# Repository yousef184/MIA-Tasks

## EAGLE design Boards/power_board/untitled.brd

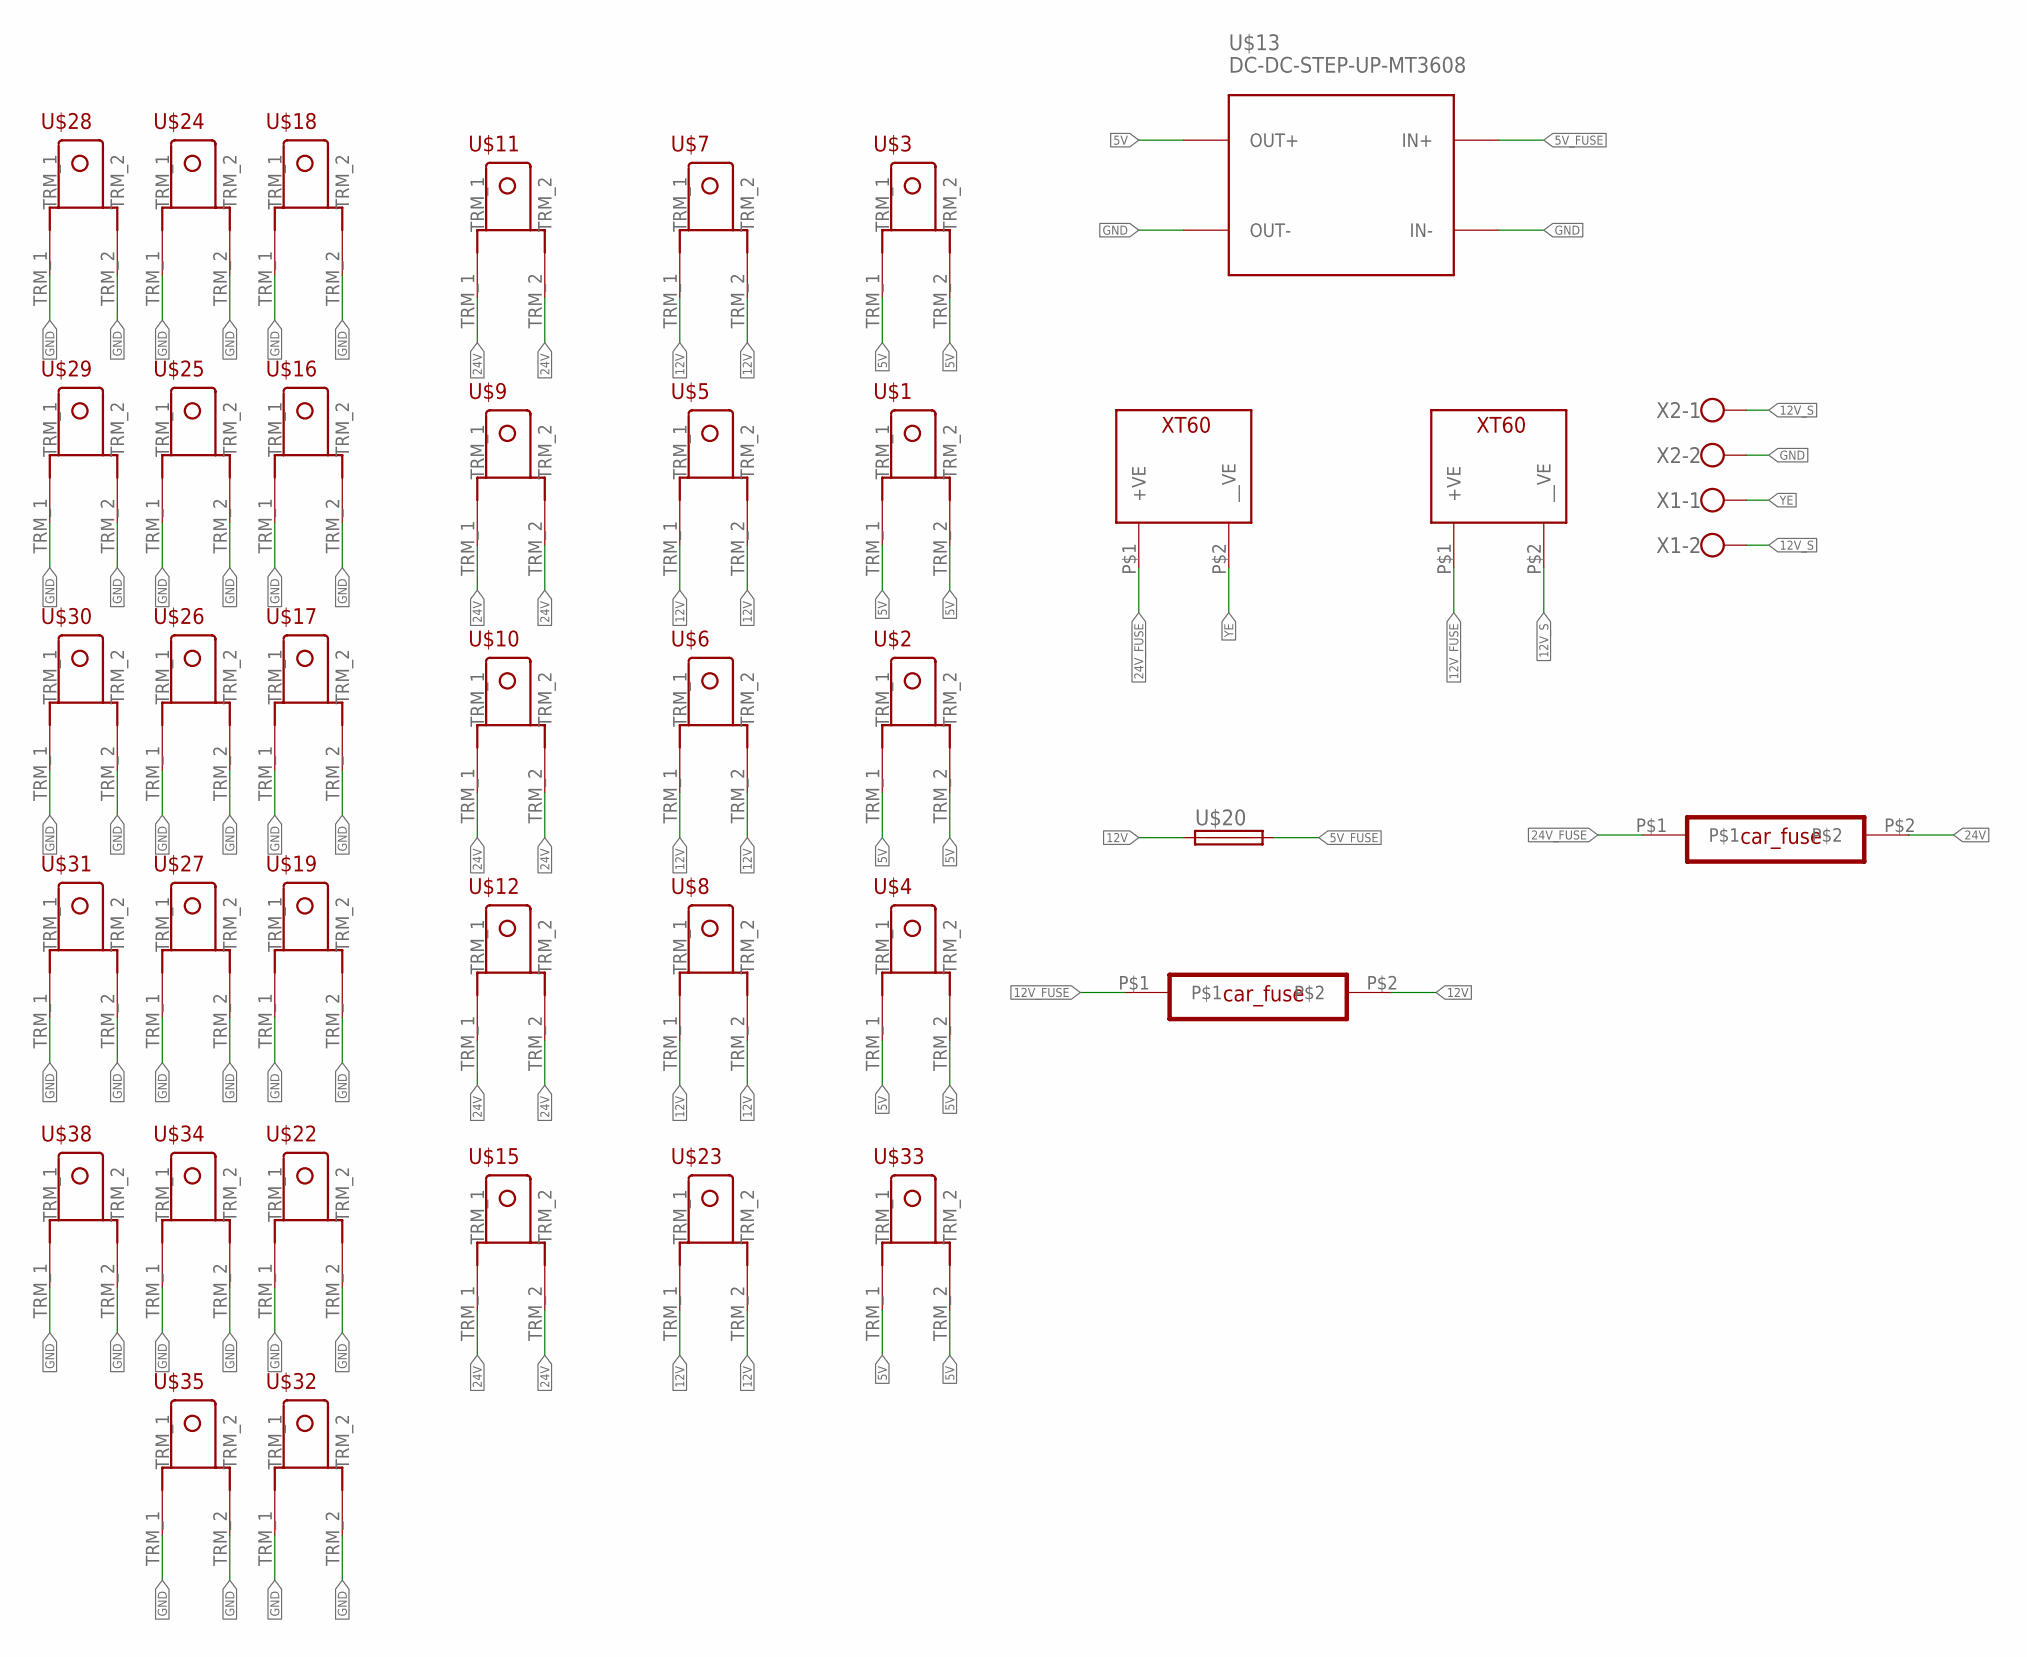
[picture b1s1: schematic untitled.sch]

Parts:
U$1, U$2, U$3, U$4, U$5, U$6, U$7, U$8, U$9, U$10, U$11, U$12, U$15, U$16, U$17, U$18, U$19, U$22, U$23, U$24, U$25, U$26, U$27, U$28, U$29, U$30, U$31, U$32, U$33, U$34, U$35, U$38: TERMINAL_EDITED
U$13: DC-DC-STEP-UP-MT3608
U$14, U$21: CAR_FUSE
U$20: FUSE_HOLDER; SH22,5A
U$36, U$37: XT60_CONNECTOR; XT60
X1, X2: ROSTA.POWER; W239-302

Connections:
5V: U$1.TRM_1, U$1.TRM_2, U$2.TRM_1, U$2.TRM_2, U$3.TRM_1, U$3.TRM_2, U$4.TRM_1, U$4.TRM_2, U$13.OUT+, U$33.TRM_1, U$33.TRM_2
5V_FUSE: U$13.IN+, U$20.2
12V: U$5.TRM_1, U$5.TRM_2, U$6.TRM_1, U$6.TRM_2, U$7.TRM_1, U$7.TRM_2, U$8.TRM_1, U$8.TRM_2, U$14.P$2, U$20.1, U$23.TRM_1, U$23.TRM_2
12V_FUSE: U$14.P$1, U$37.P$1 (+VE)
12V_S: U$37.P$2 (__VE), X1.2, X2.1
24V: U$9.TRM_1, U$9.TRM_2, U$10.TRM_1, U$10.TRM_2, U$11.TRM_1, U$11.TRM_2, U$12.TRM_1, U$12.TRM_2, U$15.TRM_1, U$15.TRM_2, U$21.P$2
24V_FUSE: U$21.P$1, U$36.P$1 (+VE)
GND: U$13.IN-, U$13.OUT-, U$16.TRM_1, U$16.TRM_2, U$17.TRM_1, U$17.TRM_2, U$18.TRM_1, U$18.TRM_2, U$19.TRM_1, U$19.TRM_2, U$22.TRM_1, U$22.TRM_2, U$24.TRM_1, U$24.TRM_2, U$25.TRM_1, U$25.TRM_2, U$26.TRM_1, U$26.TRM_2, U$27.TRM_1, U$27.TRM_2, U$28.TRM_1, U$28.TRM_2, U$29.TRM_1, U$29.TRM_2, U$30.TRM_1, U$30.TRM_2, U$31.TRM_1, U$31.TRM_2, U$32.TRM_1, U$32.TRM_2, U$34.TRM_1, U$34.TRM_2, U$35.TRM_1, U$35.TRM_2, U$38.TRM_1, U$38.TRM_2, X2.2
YE: U$36.P$2 (__VE), X1.1

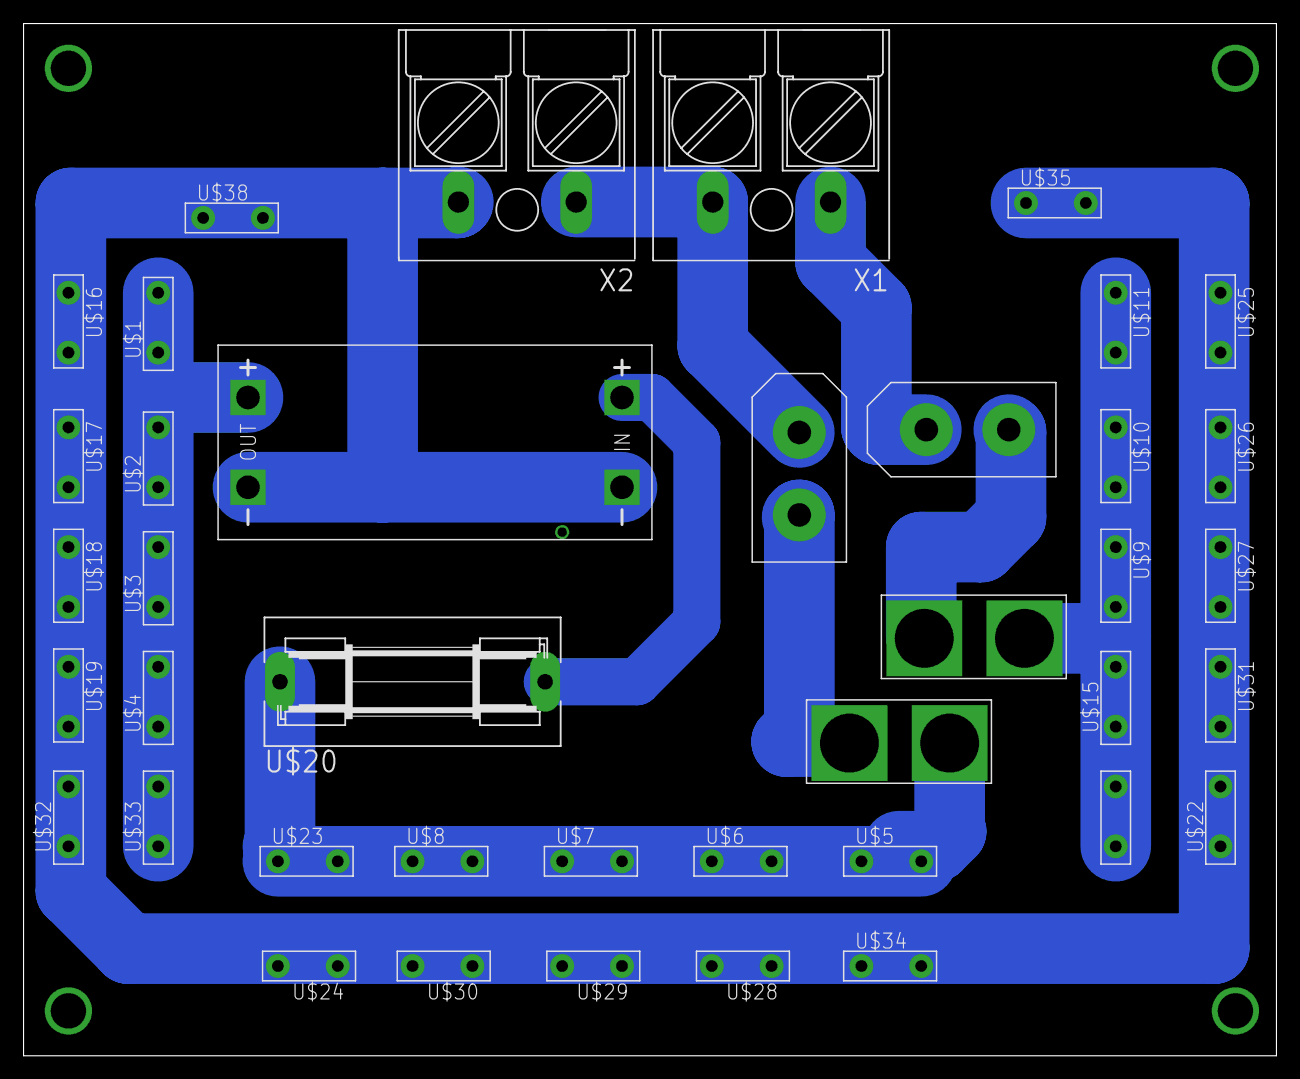
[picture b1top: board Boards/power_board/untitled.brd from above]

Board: 2 copper layers, 106.3 x 87.6 mm, 40 parts (0 on the bottom side), 9 nets.

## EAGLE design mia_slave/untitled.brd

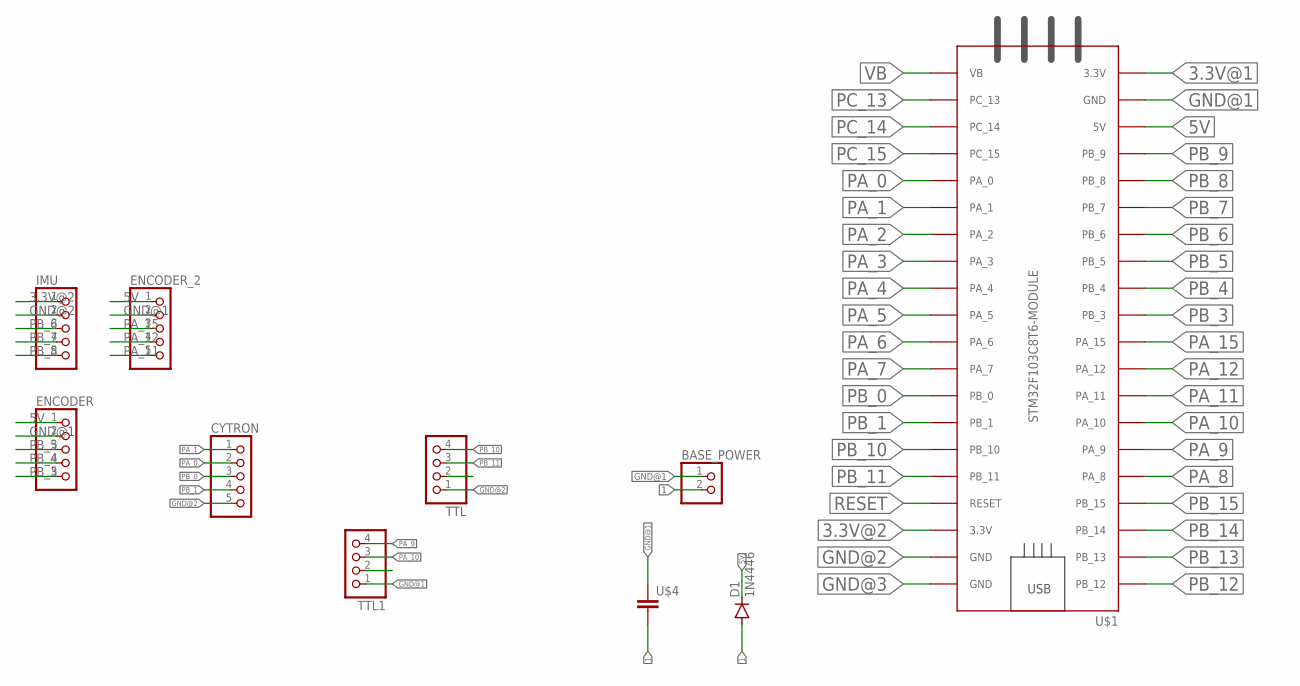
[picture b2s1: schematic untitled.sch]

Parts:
BASE_POWER: PINHD-2_DATA; 1X02_DATA
CYTRON: PINHD-5_DATA; 1X05_DATA
D1: 1N4446; DO35-10
ENCODER: PINHD-5_DATA; 1X05_DATA
ENCODER_2: PINHD-5_DATA; 1X05_DATA
IMU: PINHD-5_DATA; 1X05_DATA
TTL, TTL1: PINHD-4_DATA; 1X04_DATA
U$1: STM32F103C8T6-MODULE
U$4: CAPACITOR; C025-025X050

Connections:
1: BASE_POWER.2, D1.A, U$4.2
3.3V@1: U$1.3.3V_1 (3.3V)
3.3V@2: IMU.1, U$1.3.3V_2 (3.3V)
5V: D1.C, ENCODER.1, ENCODER_2.1, TTL.2, TTL1.2, U$1.5V
GND@1: BASE_POWER.1, ENCODER.2, ENCODER_2.2, TTL1.1, U$1.GND_1 (GND), U$4.1
GND@2: CYTRON.5, IMU.2, TTL.1, U$1.GND_2 (GND)
GND@3: U$1.GND_3 (GND)
PA_0: CYTRON.2, U$1.PA_0
PA_1: CYTRON.1, U$1.PA_1
PA_2: U$1.PA_2
PA_3: U$1.PA_3
PA_4: U$1.PA_4
PA_5: U$1.PA_5
PA_6: U$1.PA_6
PA_7: U$1.PA_7
PA_8: U$1.PA_8
PA_9: TTL1.4, U$1.PA_9
PA_10: TTL1.3, U$1.PA_10
PA_11: ENCODER_2.5, U$1.PA_11
PA_12: ENCODER_2.4, U$1.PA_12
PA_15: ENCODER_2.3, U$1.PA_15
PB_0: CYTRON.3, U$1.PB_0
PB_1: CYTRON.4, U$1.PB_1
PB_3: ENCODER.5, U$1.PB_3
PB_4: ENCODER.4, U$1.PB_4
PB_5: ENCODER.3, U$1.PB_5
PB_6: IMU.3, U$1.PB_6
PB_7: IMU.4, U$1.PB_7
PB_8: IMU.5, U$1.PB_8
PB_9: U$1.PB_9
PB_10: TTL.4, U$1.PB_10
PB_11: TTL.3, U$1.PB_11
PB_12: U$1.PB_12
PB_13: U$1.PB_13
PB_14: U$1.PB_14
PB_15: U$1.PB_15
PC_13: U$1.PC_13
PC_14: U$1.PC_14
PC_15: U$1.PC_15
RESET: U$1.RESET
VB: U$1.VB

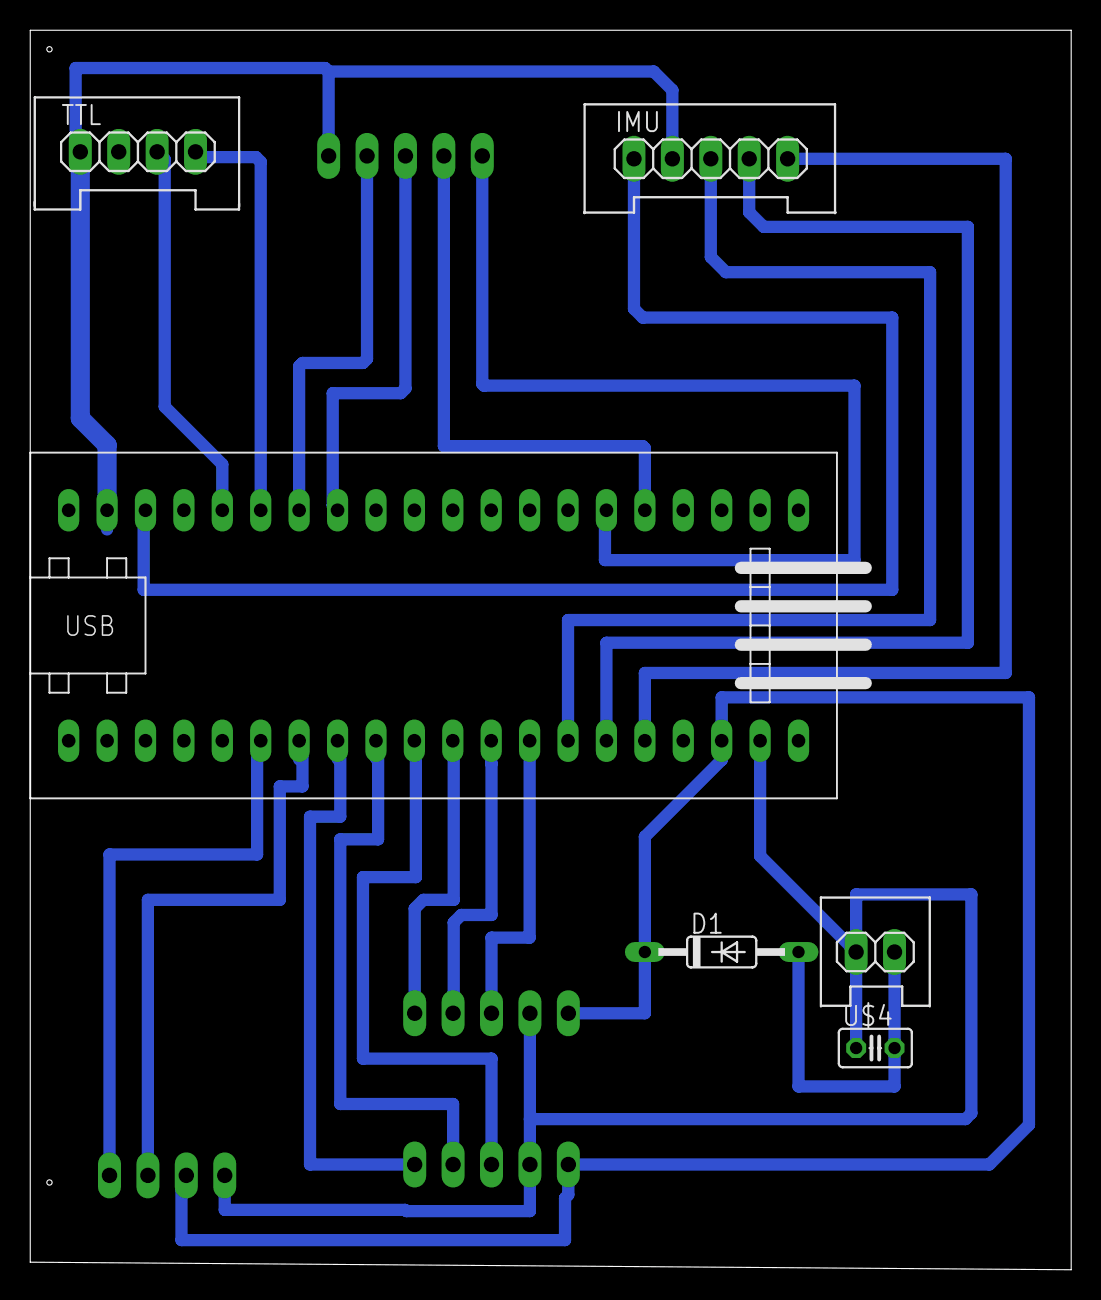
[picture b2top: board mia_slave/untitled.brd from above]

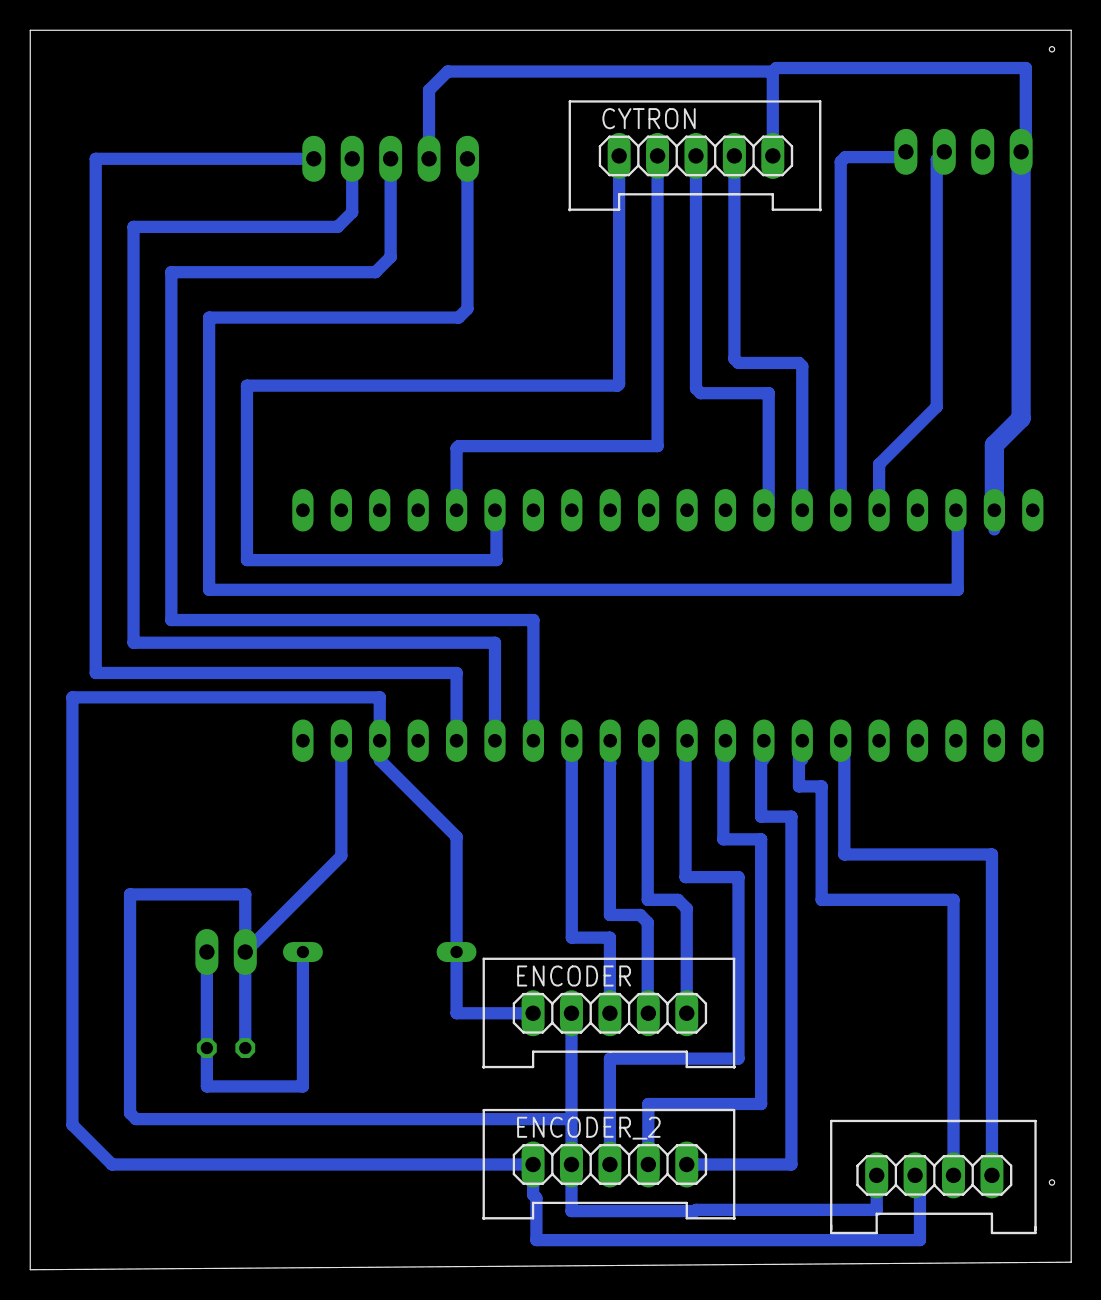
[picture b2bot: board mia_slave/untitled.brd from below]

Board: 2 copper layers, 68.8 x 82.0 mm, 10 parts (4 on the bottom side), 22 nets.
